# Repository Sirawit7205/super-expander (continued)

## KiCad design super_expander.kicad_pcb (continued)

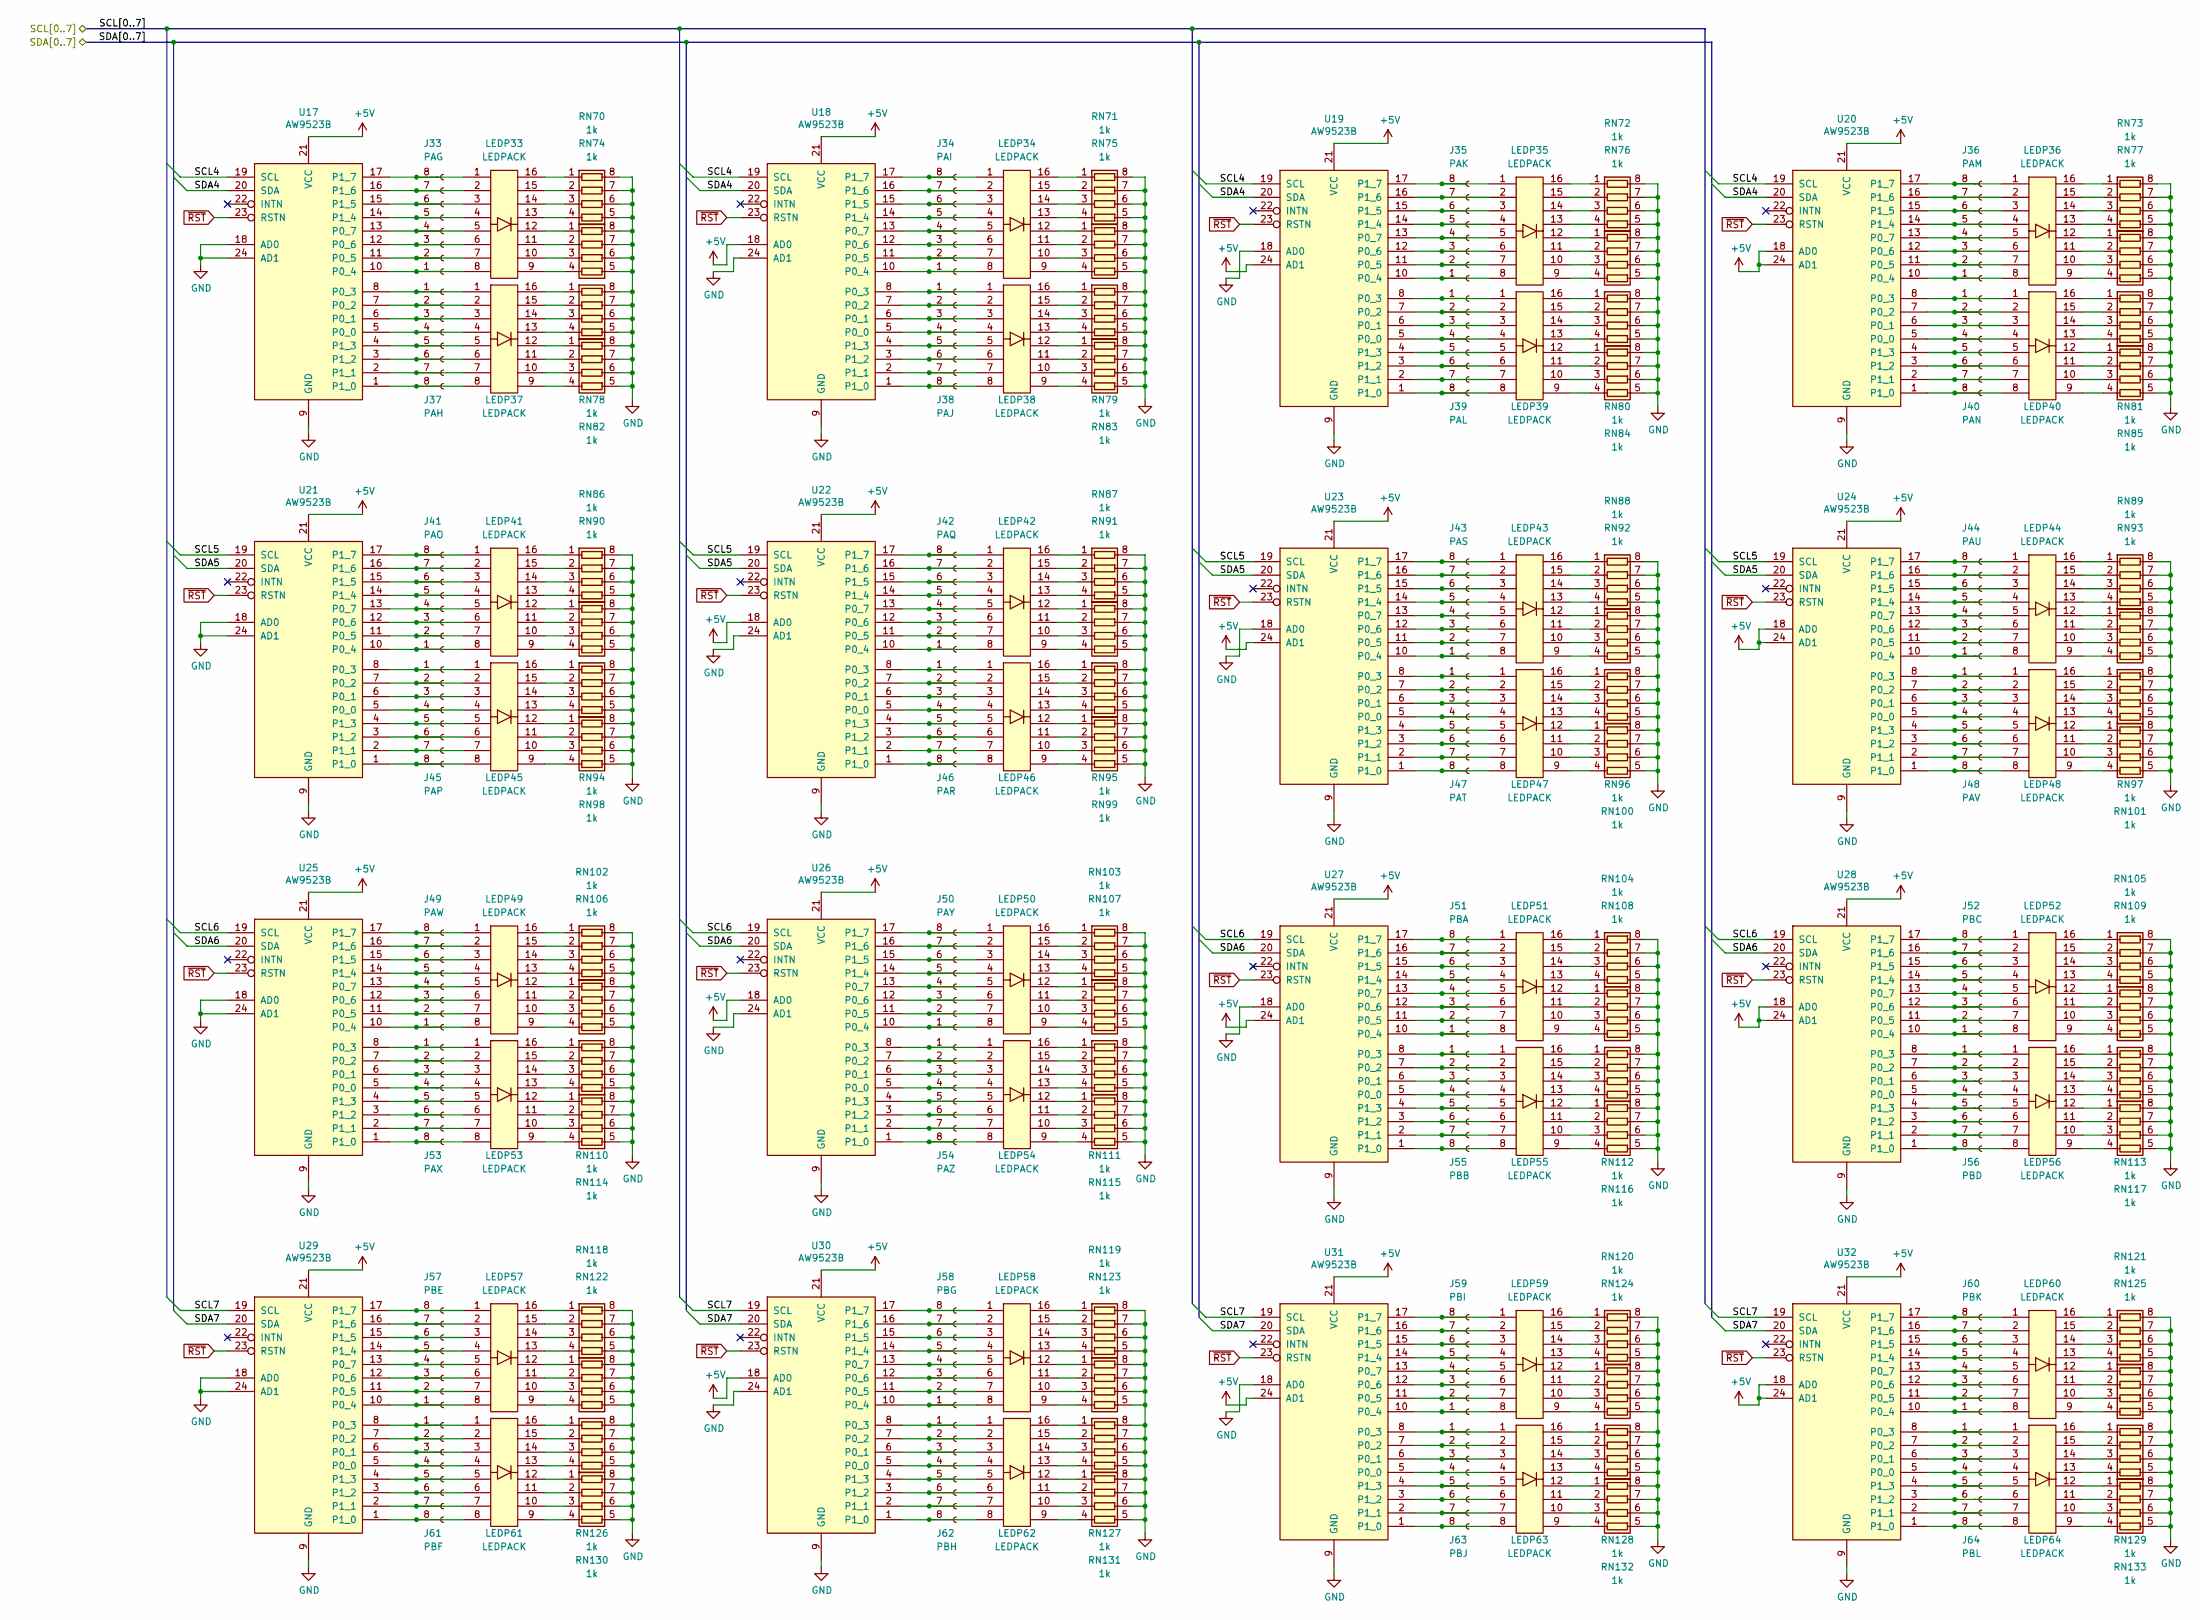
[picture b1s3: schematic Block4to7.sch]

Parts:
J33: PAG; PinHeader_1x08_P1.27mm_Vertical
J34: PAI; PinHeader_1x08_P1.27mm_Vertical
J35: PAK; PinHeader_1x08_P1.27mm_Vertical
J36: PAM; PinHeader_1x08_P1.27mm_Vertical
J37: PAH; PinHeader_1x08_P1.27mm_Vertical
J38: PAJ; PinHeader_1x08_P1.27mm_Vertical
J39: PAL; PinHeader_1x08_P1.27mm_Vertical
J40: PAN; PinHeader_1x08_P1.27mm_Vertical
J41: PAO; PinHeader_1x08_P1.27mm_Vertical
J42: PAQ; PinHeader_1x08_P1.27mm_Vertical
J43: PAS; PinHeader_1x08_P1.27mm_Vertical
J44: PAU; PinHeader_1x08_P1.27mm_Vertical
J45: PAP; PinHeader_1x08_P1.27mm_Vertical
J46: PAR; PinHeader_1x08_P1.27mm_Vertical
J47: PAT; PinHeader_1x08_P1.27mm_Vertical
J48: PAV; PinHeader_1x08_P1.27mm_Vertical
J49: PAW; PinHeader_1x08_P1.27mm_Vertical
J50: PAY; PinHeader_1x08_P1.27mm_Vertical
J51: PBA; PinHeader_1x08_P1.27mm_Vertical
J52: PBC; PinHeader_1x08_P1.27mm_Vertical
J53: PAX; PinHeader_1x08_P1.27mm_Vertical
J54: PAZ; PinHeader_1x08_P1.27mm_Vertical
J55: PBB; PinHeader_1x08_P1.27mm_Vertical
J56: PBD; PinHeader_1x08_P1.27mm_Vertical
J57: PBE; PinHeader_1x08_P1.27mm_Vertical
J58: PBG; PinHeader_1x08_P1.27mm_Vertical
J59: PBI; PinHeader_1x08_P1.27mm_Vertical
J60: PBK; PinHeader_1x08_P1.27mm_Vertical
J61: PBF; PinHeader_1x08_P1.27mm_Vertical
J62: PBH; PinHeader_1x08_P1.27mm_Vertical
J63: PBJ; PinHeader_1x08_P1.27mm_Vertical
J64: PBL; PinHeader_1x08_P1.27mm_Vertical
LEDP33, LEDP34, LEDP35, LEDP36, LEDP37, LEDP38, LEDP39, LEDP40, LEDP41, LEDP42, LEDP43, LEDP44, LEDP45, LEDP46, LEDP47, LEDP48, LEDP49, LEDP50, LEDP51, LEDP52, LEDP53, LEDP54, LEDP55, LEDP56, LEDP57, LEDP58, LEDP59, LEDP60, LEDP61, LEDP62, LEDP63, LEDP64: LEDPACK; LED_PACK_8
RN70, RN71, RN72, RN73, RN74, RN75, RN76, RN77, RN78, RN79, RN80, RN81, RN82, RN83, RN84, RN85, RN86, RN87, RN88, RN89, RN90, RN91, RN92, RN93, RN94, RN95, RN96, RN97, RN98, RN99, RN100, RN101, RN102, RN103, RN104, RN105, RN106, RN107, RN108, RN109, RN110, RN111, RN112, RN113, RN114, RN115, RN116, RN117, RN118, RN119, RN120, RN121, RN122, RN123, RN124, RN125, RN126, RN127, RN128, RN129, RN130, RN131, RN132, RN133: 1k; R_Array_Convex_4x0402
U17, U18, U19, U20, U21, U22, U23, U24, U25, U26, U27, U28, U29, U30, U31, U32: AW9523B; QFN-24-1EP_4x4mm_P0.5mm_EP2.7x2.7mm_ThermalVias

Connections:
+5V: U17.21 (VCC), U18.18 (AD0), U18.21 (VCC), U19.21 (VCC), U19.24 (AD1), U20.18 (AD0), U20.21 (VCC), U20.24 (AD1), U21.21 (VCC), U22.18 (AD0), U22.21 (VCC), U23.21 (VCC), U23.24 (AD1), U24.18 (AD0), U24.21 (VCC), U24.24 (AD1), U25.21 (VCC), U26.18 (AD0), U26.21 (VCC), U27.21 (VCC), U27.24 (AD1), U28.18 (AD0), U28.21 (VCC), U28.24 (AD1), U29.21 (VCC), U30.18 (AD0), U30.21 (VCC), U31.21 (VCC), U31.24 (AD1), U32.18 (AD0), U32.21 (VCC), U32.24 (AD1); also elsewhere on the board
/SCL4: U17.19 (SCL), U18.19 (SCL), U19.19 (SCL), U20.19 (SCL); also elsewhere on the board
/SCL5: U21.19 (SCL), U22.19 (SCL), U23.19 (SCL), U24.19 (SCL); also elsewhere on the board
/SCL6: U25.19 (SCL), U26.19 (SCL), U27.19 (SCL), U28.19 (SCL); also elsewhere on the board
/SCL7: U29.19 (SCL), U30.19 (SCL), U31.19 (SCL), U32.19 (SCL); also elsewhere on the board
/SDA4: U17.20 (SDA), U18.20 (SDA), U19.20 (SDA), U20.20 (SDA); also elsewhere on the board
/SDA5: U21.20 (SDA), U22.20 (SDA), U23.20 (SDA), U24.20 (SDA); also elsewhere on the board
/SDA6: U25.20 (SDA), U26.20 (SDA), U27.20 (SDA), U28.20 (SDA); also elsewhere on the board
/SDA7: U29.20 (SDA), U30.20 (SDA), U31.20 (SDA), U32.20 (SDA); also elsewhere on the board
GND: RN70.5 (R4.2), RN70.6 (R3.2), RN70.7 (R2.2), RN70.8 (R1.2), RN71.5 (R4.2), RN71.6 (R3.2), RN71.7 (R2.2), RN71.8 (R1.2), RN72.5 (R4.2), RN72.6 (R3.2), RN72.7 (R2.2), RN72.8 (R1.2), RN73.5 (R4.2), RN73.6 (R3.2), RN73.7 (R2.2), RN73.8 (R1.2), RN74.5 (R4.2), RN74.6 (R3.2), RN74.7 (R2.2), RN74.8 (R1.2), RN75.5 (R4.2), RN75.6 (R3.2), RN75.7 (R2.2), RN75.8 (R1.2), RN76.5 (R4.2), RN76.6 (R3.2), RN76.7 (R2.2), RN76.8 (R1.2), RN77.5 (R4.2), RN77.6 (R3.2), RN77.7 (R2.2), RN77.8 (R1.2), RN78.5 (R4.2), RN78.6 (R3.2), RN78.7 (R2.2), RN78.8 (R1.2), RN79.5 (R4.2), RN79.6 (R3.2), RN79.7 (R2.2), RN79.8 (R1.2), RN80.5 (R4.2), RN80.6 (R3.2), RN80.7 (R2.2), RN80.8 (R1.2), RN81.5 (R4.2), RN81.6 (R3.2), RN81.7 (R2.2), RN81.8 (R1.2), RN82.5 (R4.2), RN82.6 (R3.2), RN82.7 (R2.2), RN82.8 (R1.2), RN83.5 (R4.2), RN83.6 (R3.2), RN83.7 (R2.2), RN83.8 (R1.2), RN84.5 (R4.2), RN84.6 (R3.2), RN84.7 (R2.2), RN84.8 (R1.2), RN85.5 (R4.2), RN85.6 (R3.2), RN85.7 (R2.2), RN85.8 (R1.2), RN86.5 (R4.2), RN86.6 (R3.2), RN86.7 (R2.2), RN86.8 (R1.2), RN87.5 (R4.2), RN87.6 (R3.2), RN87.7 (R2.2), RN87.8 (R1.2), RN88.5 (R4.2), RN88.6 (R3.2), RN88.7 (R2.2), RN88.8 (R1.2), RN89.5 (R4.2), RN89.6 (R3.2), RN89.7 (R2.2), RN89.8 (R1.2), RN90.5 (R4.2), RN90.6 (R3.2), RN90.7 (R2.2), RN90.8 (R1.2), RN91.5 (R4.2), RN91.6 (R3.2), RN91.7 (R2.2), RN91.8 (R1.2), RN92.5 (R4.2), RN92.6 (R3.2), RN92.7 (R2.2), RN92.8 (R1.2), RN93.5 (R4.2), RN93.6 (R3.2), RN93.7 (R2.2), RN93.8 (R1.2), RN94.5 (R4.2), RN94.6 (R3.2), RN94.7 (R2.2), RN94.8 (R1.2), RN95.5 (R4.2), RN95.6 (R3.2), RN95.7 (R2.2), RN95.8 (R1.2), RN96.5 (R4.2), RN96.6 (R3.2), RN96.7 (R2.2), RN96.8 (R1.2), RN97.5 (R4.2), RN97.6 (R3.2), RN97.7 (R2.2), RN97.8 (R1.2), RN98.5 (R4.2), RN98.6 (R3.2), RN98.7 (R2.2), RN98.8 (R1.2), RN99.5 (R4.2), RN99.6 (R3.2), RN99.7 (R2.2), RN99.8 (R1.2), RN100.5 (R4.2), RN100.6 (R3.2), RN100.7 (R2.2), RN100.8 (R1.2), RN101.5 (R4.2), RN101.6 (R3.2), RN101.7 (R2.2), RN101.8 (R1.2), RN102.5 (R4.2), RN102.6 (R3.2), RN102.7 (R2.2), RN102.8 (R1.2), RN103.5 (R4.2), RN103.6 (R3.2), RN103.7 (R2.2), RN103.8 (R1.2), RN104.5 (R4.2), RN104.6 (R3.2), RN104.7 (R2.2), RN104.8 (R1.2), RN105.5 (R4.2), RN105.6 (R3.2), RN105.7 (R2.2), RN105.8 (R1.2), RN106.5 (R4.2), RN106.6 (R3.2), RN106.7 (R2.2), RN106.8 (R1.2), RN107.5 (R4.2), RN107.6 (R3.2), RN107.7 (R2.2), RN107.8 (R1.2), RN108.5 (R4.2), RN108.6 (R3.2), RN108.7 (R2.2), RN108.8 (R1.2), RN109.5 (R4.2), RN109.6 (R3.2), RN109.7 (R2.2), RN109.8 (R1.2), RN110.5 (R4.2), RN110.6 (R3.2), RN110.7 (R2.2), RN110.8 (R1.2), RN111.5 (R4.2), RN111.6 (R3.2), RN111.7 (R2.2), RN111.8 (R1.2), RN112.5 (R4.2), RN112.6 (R3.2), RN112.7 (R2.2), RN112.8 (R1.2), RN113.5 (R4.2), RN113.6 (R3.2), RN113.7 (R2.2), RN113.8 (R1.2), RN114.5 (R4.2), RN114.6 (R3.2), RN114.7 (R2.2), RN114.8 (R1.2), RN115.5 (R4.2), RN115.6 (R3.2), RN115.7 (R2.2), RN115.8 (R1.2), RN116.5 (R4.2), RN116.6 (R3.2), RN116.7 (R2.2), RN116.8 (R1.2), RN117.5 (R4.2), RN117.6 (R3.2), RN117.7 (R2.2), RN117.8 (R1.2), RN118.5 (R4.2), RN118.6 (R3.2), RN118.7 (R2.2), RN118.8 (R1.2), RN119.5 (R4.2), RN119.6 (R3.2), RN119.7 (R2.2), RN119.8 (R1.2), RN120.5 (R4.2), RN120.6 (R3.2), RN120.7 (R2.2), RN120.8 (R1.2), RN121.5 (R4.2), RN121.6 (R3.2), RN121.7 (R2.2), RN121.8 (R1.2), RN122.5 (R4.2), RN122.6 (R3.2), RN122.7 (R2.2), RN122.8 (R1.2), RN123.5 (R4.2), RN123.6 (R3.2), RN123.7 (R2.2), RN123.8 (R1.2), RN124.5 (R4.2), RN124.6 (R3.2), RN124.7 (R2.2), RN124.8 (R1.2), RN125.5 (R4.2), RN125.6 (R3.2), RN125.7 (R2.2), RN125.8 (R1.2), RN126.5 (R4.2), RN126.6 (R3.2), RN126.7 (R2.2), RN126.8 (R1.2), RN127.5 (R4.2), RN127.6 (R3.2), RN127.7 (R2.2), RN127.8 (R1.2), RN128.5 (R4.2), RN128.6 (R3.2), RN128.7 (R2.2), RN128.8 (R1.2), RN129.5 (R4.2), RN129.6 (R3.2), RN129.7 (R2.2), RN129.8 (R1.2), RN130.5 (R4.2), RN130.6 (R3.2), RN130.7 (R2.2), RN130.8 (R1.2), RN131.5 (R4.2), RN131.6 (R3.2), RN131.7 (R2.2), RN131.8 (R1.2), RN132.5 (R4.2), RN132.6 (R3.2), RN132.7 (R2.2), RN132.8 (R1.2), RN133.5 (R4.2), RN133.6 (R3.2), RN133.7 (R2.2), RN133.8 (R1.2), U17.9 (GND), U17.18 (AD0), U17.24 (AD1), U17.25 (GND), U18.9 (GND), U18.24 (AD1), U18.25 (GND), U19.9 (GND), U19.18 (AD0), U19.25 (GND), U20.9 (GND), U20.25 (GND), U21.9 (GND), U21.18 (AD0), U21.24 (AD1), U21.25 (GND), U22.9 (GND), U22.24 (AD1), U22.25 (GND), U23.9 (GND), U23.18 (AD0), U23.25 (GND), U24.9 (GND), U24.25 (GND), U25.9 (GND), U25.18 (AD0), U25.24 (AD1), U25.25 (GND), U26.9 (GND), U26.24 (AD1), U26.25 (GND), U27.9 (GND), U27.18 (AD0), U27.25 (GND), U28.9 (GND), U28.25 (GND), U29.9 (GND), U29.18 (AD0), U29.24 (AD1), U29.25 (GND), U30.9 (GND), U30.24 (AD1), U30.25 (GND), U31.9 (GND), U31.18 (AD0), U31.25 (GND), U32.9 (GND), U32.25 (GND); also elsewhere on the board
unnamed: J33.1, LEDP33.8, U17.10 (P0_4)
unnamed: J33.2, LEDP33.7, U17.11 (P0_5)
unnamed: J33.3, LEDP33.6, U17.12 (P0_6)
unnamed: J33.4, LEDP33.5, U17.13 (P0_7)
unnamed: J33.5, LEDP33.4, U17.14 (P1_4)
unnamed: J33.6, LEDP33.3, U17.15 (P1_5)
unnamed: J33.7, LEDP33.2, U17.16 (P1_6)
unnamed: J33.8, LEDP33.1, U17.17 (P1_7)
unnamed: J34.1, LEDP34.8, U18.10 (P0_4)
unnamed: J34.2, LEDP34.7, U18.11 (P0_5)
unnamed: J34.3, LEDP34.6, U18.12 (P0_6)
unnamed: J34.4, LEDP34.5, U18.13 (P0_7)
unnamed: J34.5, LEDP34.4, U18.14 (P1_4)
unnamed: J34.6, LEDP34.3, U18.15 (P1_5)
unnamed: J34.7, LEDP34.2, U18.16 (P1_6)
unnamed: J34.8, LEDP34.1, U18.17 (P1_7)
unnamed: J35.1, LEDP35.8, U19.10 (P0_4)
unnamed: J35.2, LEDP35.7, U19.11 (P0_5)
unnamed: J35.3, LEDP35.6, U19.12 (P0_6)
unnamed: J35.4, LEDP35.5, U19.13 (P0_7)
unnamed: J35.5, LEDP35.4, U19.14 (P1_4)
unnamed: J35.6, LEDP35.3, U19.15 (P1_5)
unnamed: J35.7, LEDP35.2, U19.16 (P1_6)
unnamed: J35.8, LEDP35.1, U19.17 (P1_7)
unnamed: J36.1, LEDP36.8, U20.10 (P0_4)
unnamed: J36.2, LEDP36.7, U20.11 (P0_5)
unnamed: J36.3, LEDP36.6, U20.12 (P0_6)
unnamed: J36.4, LEDP36.5, U20.13 (P0_7)
unnamed: J36.5, LEDP36.4, U20.14 (P1_4)
unnamed: J36.6, LEDP36.3, U20.15 (P1_5)
unnamed: J36.7, LEDP36.2, U20.16 (P1_6)
unnamed: J36.8, LEDP36.1, U20.17 (P1_7)
unnamed: J37.1, LEDP37.1, U17.8 (P0_3)
unnamed: J37.2, LEDP37.2, U17.7 (P0_2)
unnamed: J37.3, LEDP37.3, U17.6 (P0_1)
unnamed: J37.4, LEDP37.4, U17.5 (P0_0)
unnamed: J37.5, LEDP37.5, U17.4 (P1_3)
unnamed: J37.6, LEDP37.6, U17.3 (P1_2)
unnamed: J37.7, LEDP37.7, U17.2 (P1_1)
unnamed: J37.8, LEDP37.8, U17.1 (P1_0)
unnamed: J38.1, LEDP38.1, U18.8 (P0_3)
unnamed: J38.2, LEDP38.2, U18.7 (P0_2)
unnamed: J38.3, LEDP38.3, U18.6 (P0_1)
unnamed: J38.4, LEDP38.4, U18.5 (P0_0)
unnamed: J38.5, LEDP38.5, U18.4 (P1_3)
unnamed: J38.6, LEDP38.6, U18.3 (P1_2)
unnamed: J38.7, LEDP38.7, U18.2 (P1_1)
unnamed: J38.8, LEDP38.8, U18.1 (P1_0)
unnamed: J39.1, LEDP39.1, U19.8 (P0_3)
unnamed: J39.2, LEDP39.2, U19.7 (P0_2)
unnamed: J39.3, LEDP39.3, U19.6 (P0_1)
unnamed: J39.4, LEDP39.4, U19.5 (P0_0)
unnamed: J39.5, LEDP39.5, U19.4 (P1_3)
unnamed: J39.6, LEDP39.6, U19.3 (P1_2)
unnamed: J39.7, LEDP39.7, U19.2 (P1_1)
unnamed: J39.8, LEDP39.8, U19.1 (P1_0)
unnamed: J40.1, LEDP40.1, U20.8 (P0_3)
unnamed: J40.2, LEDP40.2, U20.7 (P0_2)
unnamed: J40.3, LEDP40.3, U20.6 (P0_1)
unnamed: J40.4, LEDP40.4, U20.5 (P0_0)
unnamed: J40.5, LEDP40.5, U20.4 (P1_3)
unnamed: J40.6, LEDP40.6, U20.3 (P1_2)
unnamed: J40.7, LEDP40.7, U20.2 (P1_1)
unnamed: J40.8, LEDP40.8, U20.1 (P1_0)
unnamed: J41.1, LEDP41.8, U21.10 (P0_4)
unnamed: J41.2, LEDP41.7, U21.11 (P0_5)
unnamed: J41.3, LEDP41.6, U21.12 (P0_6)
unnamed: J41.4, LEDP41.5, U21.13 (P0_7)
unnamed: J41.5, LEDP41.4, U21.14 (P1_4)
unnamed: J41.6, LEDP41.3, U21.15 (P1_5)
unnamed: J41.7, LEDP41.2, U21.16 (P1_6)
unnamed: J41.8, LEDP41.1, U21.17 (P1_7)
unnamed: J42.1, LEDP42.8, U22.10 (P0_4)
unnamed: J42.2, LEDP42.7, U22.11 (P0_5)
unnamed: J42.3, LEDP42.6, U22.12 (P0_6)
unnamed: J42.4, LEDP42.5, U22.13 (P0_7)
unnamed: J42.5, LEDP42.4, U22.14 (P1_4)
unnamed: J42.6, LEDP42.3, U22.15 (P1_5)
unnamed: J42.7, LEDP42.2, U22.16 (P1_6)
unnamed: J42.8, LEDP42.1, U22.17 (P1_7)
unnamed: J43.1, LEDP43.8, U23.10 (P0_4)
unnamed: J43.2, LEDP43.7, U23.11 (P0_5)
unnamed: J43.3, LEDP43.6, U23.12 (P0_6)
unnamed: J43.4, LEDP43.5, U23.13 (P0_7)
unnamed: J43.5, LEDP43.4, U23.14 (P1_4)
unnamed: J43.6, LEDP43.3, U23.15 (P1_5)
unnamed: J43.7, LEDP43.2, U23.16 (P1_6)
unnamed: J43.8, LEDP43.1, U23.17 (P1_7)
unnamed: J44.1, LEDP44.8, U24.10 (P0_4)
unnamed: J44.2, LEDP44.7, U24.11 (P0_5)
unnamed: J44.3, LEDP44.6, U24.12 (P0_6)
unnamed: J44.4, LEDP44.5, U24.13 (P0_7)
unnamed: J44.5, LEDP44.4, U24.14 (P1_4)
unnamed: J44.6, LEDP44.3, U24.15 (P1_5)
unnamed: J44.7, LEDP44.2, U24.16 (P1_6)
unnamed: J44.8, LEDP44.1, U24.17 (P1_7)
unnamed: J45.1, LEDP45.1, U21.8 (P0_3)
unnamed: J45.2, LEDP45.2, U21.7 (P0_2)
unnamed: J45.3, LEDP45.3, U21.6 (P0_1)
unnamed: J45.4, LEDP45.4, U21.5 (P0_0)
unnamed: J45.5, LEDP45.5, U21.4 (P1_3)
unnamed: J45.6, LEDP45.6, U21.3 (P1_2)
unnamed: J45.7, LEDP45.7, U21.2 (P1_1)
unnamed: J45.8, LEDP45.8, U21.1 (P1_0)
unnamed: J46.1, LEDP46.1, U22.8 (P0_3)
unnamed: J46.2, LEDP46.2, U22.7 (P0_2)
unnamed: J46.3, LEDP46.3, U22.6 (P0_1)
unnamed: J46.4, LEDP46.4, U22.5 (P0_0)
unnamed: J46.5, LEDP46.5, U22.4 (P1_3)
unnamed: J46.6, LEDP46.6, U22.3 (P1_2)
unnamed: J46.7, LEDP46.7, U22.2 (P1_1)
unnamed: J46.8, LEDP46.8, U22.1 (P1_0)
unnamed: J47.1, LEDP47.1, U23.8 (P0_3)
unnamed: J47.2, LEDP47.2, U23.7 (P0_2)
unnamed: J47.3, LEDP47.3, U23.6 (P0_1)
unnamed: J47.4, LEDP47.4, U23.5 (P0_0)
unnamed: J47.5, LEDP47.5, U23.4 (P1_3)
unnamed: J47.6, LEDP47.6, U23.3 (P1_2)
unnamed: J47.7, LEDP47.7, U23.2 (P1_1)
unnamed: J47.8, LEDP47.8, U23.1 (P1_0)
unnamed: J48.1, LEDP48.1, U24.8 (P0_3)
unnamed: J48.2, LEDP48.2, U24.7 (P0_2)
unnamed: J48.3, LEDP48.3, U24.6 (P0_1)
unnamed: J48.4, LEDP48.4, U24.5 (P0_0)
unnamed: J48.5, LEDP48.5, U24.4 (P1_3)
unnamed: J48.6, LEDP48.6, U24.3 (P1_2)
unnamed: J48.7, LEDP48.7, U24.2 (P1_1)
unnamed: J48.8, LEDP48.8, U24.1 (P1_0)
unnamed: J49.1, LEDP49.8, U25.10 (P0_4)
unnamed: J49.2, LEDP49.7, U25.11 (P0_5)
unnamed: J49.3, LEDP49.6, U25.12 (P0_6)
unnamed: J49.4, LEDP49.5, U25.13 (P0_7)
unnamed: J49.5, LEDP49.4, U25.14 (P1_4)
unnamed: J49.6, LEDP49.3, U25.15 (P1_5)
unnamed: J49.7, LEDP49.2, U25.16 (P1_6)
unnamed: J49.8, LEDP49.1, U25.17 (P1_7)
unnamed: J50.1, LEDP50.8, U26.10 (P0_4)
unnamed: J50.2, LEDP50.7, U26.11 (P0_5)
unnamed: J50.3, LEDP50.6, U26.12 (P0_6)
unnamed: J50.4, LEDP50.5, U26.13 (P0_7)
unnamed: J50.5, LEDP50.4, U26.14 (P1_4)
unnamed: J50.6, LEDP50.3, U26.15 (P1_5)
unnamed: J50.7, LEDP50.2, U26.16 (P1_6)
unnamed: J50.8, LEDP50.1, U26.17 (P1_7)
unnamed: J51.1, LEDP51.8, U27.10 (P0_4)
unnamed: J51.2, LEDP51.7, U27.11 (P0_5)
unnamed: J51.3, LEDP51.6, U27.12 (P0_6)
unnamed: J51.4, LEDP51.5, U27.13 (P0_7)
unnamed: J51.5, LEDP51.4, U27.14 (P1_4)
unnamed: J51.6, LEDP51.3, U27.15 (P1_5)
unnamed: J51.7, LEDP51.2, U27.16 (P1_6)
unnamed: J51.8, LEDP51.1, U27.17 (P1_7)
unnamed: J52.1, LEDP52.8, U28.10 (P0_4)
unnamed: J52.2, LEDP52.7, U28.11 (P0_5)
unnamed: J52.3, LEDP52.6, U28.12 (P0_6)
unnamed: J52.4, LEDP52.5, U28.13 (P0_7)
unnamed: J52.5, LEDP52.4, U28.14 (P1_4)
unnamed: J52.6, LEDP52.3, U28.15 (P1_5)
unnamed: J52.7, LEDP52.2, U28.16 (P1_6)
unnamed: J52.8, LEDP52.1, U28.17 (P1_7)
unnamed: J53.1, LEDP53.1, U25.8 (P0_3)
unnamed: J53.2, LEDP53.2, U25.7 (P0_2)
unnamed: J53.3, LEDP53.3, U25.6 (P0_1)
unnamed: J53.4, LEDP53.4, U25.5 (P0_0)
unnamed: J53.5, LEDP53.5, U25.4 (P1_3)
unnamed: J53.6, LEDP53.6, U25.3 (P1_2)
unnamed: J53.7, LEDP53.7, U25.2 (P1_1)
unnamed: J53.8, LEDP53.8, U25.1 (P1_0)
unnamed: J54.1, LEDP54.1, U26.8 (P0_3)
unnamed: J54.2, LEDP54.2, U26.7 (P0_2)
unnamed: J54.3, LEDP54.3, U26.6 (P0_1)
unnamed: J54.4, LEDP54.4, U26.5 (P0_0)
unnamed: J54.5, LEDP54.5, U26.4 (P1_3)
unnamed: J54.6, LEDP54.6, U26.3 (P1_2)
unnamed: J54.7, LEDP54.7, U26.2 (P1_1)
unnamed: J54.8, LEDP54.8, U26.1 (P1_0)
unnamed: J55.1, LEDP55.1, U27.8 (P0_3)
unnamed: J55.2, LEDP55.2, U27.7 (P0_2)
unnamed: J55.3, LEDP55.3, U27.6 (P0_1)
unnamed: J55.4, LEDP55.4, U27.5 (P0_0)
unnamed: J55.5, LEDP55.5, U27.4 (P1_3)
unnamed: J55.6, LEDP55.6, U27.3 (P1_2)
unnamed: J55.7, LEDP55.7, U27.2 (P1_1)
unnamed: J55.8, LEDP55.8, U27.1 (P1_0)
unnamed: J56.1, LEDP56.1, U28.8 (P0_3)
unnamed: J56.2, LEDP56.2, U28.7 (P0_2)
unnamed: J56.3, LEDP56.3, U28.6 (P0_1)
unnamed: J56.4, LEDP56.4, U28.5 (P0_0)
unnamed: J56.5, LEDP56.5, U28.4 (P1_3)
unnamed: J56.6, LEDP56.6, U28.3 (P1_2)
unnamed: J56.7, LEDP56.7, U28.2 (P1_1)
unnamed: J56.8, LEDP56.8, U28.1 (P1_0)
unnamed: J57.1, LEDP57.8, U29.10 (P0_4)
unnamed: J57.2, LEDP57.7, U29.11 (P0_5)
unnamed: J57.3, LEDP57.6, U29.12 (P0_6)
unnamed: J57.4, LEDP57.5, U29.13 (P0_7)
unnamed: J57.5, LEDP57.4, U29.14 (P1_4)
unnamed: J57.6, LEDP57.3, U29.15 (P1_5)
unnamed: J57.7, LEDP57.2, U29.16 (P1_6)
unnamed: J57.8, LEDP57.1, U29.17 (P1_7)
unnamed: J58.1, LEDP58.8, U30.10 (P0_4)
unnamed: J58.2, LEDP58.7, U30.11 (P0_5)
unnamed: J58.3, LEDP58.6, U30.12 (P0_6)
unnamed: J58.4, LEDP58.5, U30.13 (P0_7)
unnamed: J58.5, LEDP58.4, U30.14 (P1_4)
unnamed: J58.6, LEDP58.3, U30.15 (P1_5)
unnamed: J58.7, LEDP58.2, U30.16 (P1_6)
unnamed: J58.8, LEDP58.1, U30.17 (P1_7)
unnamed: J59.1, LEDP59.8, U31.10 (P0_4)
unnamed: J59.2, LEDP59.7, U31.11 (P0_5)
unnamed: J59.3, LEDP59.6, U31.12 (P0_6)
unnamed: J59.4, LEDP59.5, U31.13 (P0_7)
unnamed: J59.5, LEDP59.4, U31.14 (P1_4)
unnamed: J59.6, LEDP59.3, U31.15 (P1_5)
unnamed: J59.7, LEDP59.2, U31.16 (P1_6)
unnamed: J59.8, LEDP59.1, U31.17 (P1_7)
unnamed: J60.1, LEDP60.8, U32.10 (P0_4)
unnamed: J60.2, LEDP60.7, U32.11 (P0_5)
unnamed: J60.3, LEDP60.6, U32.12 (P0_6)
unnamed: J60.4, LEDP60.5, U32.13 (P0_7)
unnamed: J60.5, LEDP60.4, U32.14 (P1_4)
unnamed: J60.6, LEDP60.3, U32.15 (P1_5)
unnamed: J60.7, LEDP60.2, U32.16 (P1_6)
unnamed: J60.8, LEDP60.1, U32.17 (P1_7)
unnamed: J61.1, LEDP61.1, U29.8 (P0_3)
unnamed: J61.2, LEDP61.2, U29.7 (P0_2)
unnamed: J61.3, LEDP61.3, U29.6 (P0_1)
unnamed: J61.4, LEDP61.4, U29.5 (P0_0)
unnamed: J61.5, LEDP61.5, U29.4 (P1_3)
unnamed: J61.6, LEDP61.6, U29.3 (P1_2)
unnamed: J61.7, LEDP61.7, U29.2 (P1_1)
unnamed: J61.8, LEDP61.8, U29.1 (P1_0)
unnamed: J62.1, LEDP62.1, U30.8 (P0_3)
unnamed: J62.2, LEDP62.2, U30.7 (P0_2)
unnamed: J62.3, LEDP62.3, U30.6 (P0_1)
unnamed: J62.4, LEDP62.4, U30.5 (P0_0)
unnamed: J62.5, LEDP62.5, U30.4 (P1_3)
unnamed: J62.6, LEDP62.6, U30.3 (P1_2)
unnamed: J62.7, LEDP62.7, U30.2 (P1_1)
unnamed: J62.8, LEDP62.8, U30.1 (P1_0)
unnamed: J63.1, LEDP63.1, U31.8 (P0_3)
unnamed: J63.2, LEDP63.2, U31.7 (P0_2)
unnamed: J63.3, LEDP63.3, U31.6 (P0_1)
unnamed: J63.4, LEDP63.4, U31.5 (P0_0)
unnamed: J63.5, LEDP63.5, U31.4 (P1_3)
unnamed: J63.6, LEDP63.6, U31.3 (P1_2)
unnamed: J63.7, LEDP63.7, U31.2 (P1_1)
unnamed: J63.8, LEDP63.8, U31.1 (P1_0)
unnamed: J64.1, LEDP64.1, U32.8 (P0_3)
unnamed: J64.2, LEDP64.2, U32.7 (P0_2)
unnamed: J64.3, LEDP64.3, U32.6 (P0_1)
unnamed: J64.4, LEDP64.4, U32.5 (P0_0)
unnamed: J64.5, LEDP64.5, U32.4 (P1_3)
unnamed: J64.6, LEDP64.6, U32.3 (P1_2)
unnamed: J64.7, LEDP64.7, U32.2 (P1_1)
unnamed: J64.8, LEDP64.8, U32.1 (P1_0)
unnamed: LEDP33.9, RN74.4 (R4.1)
unnamed: LEDP33.10, RN74.3 (R3.1)
unnamed: LEDP33.11, RN74.2 (R2.1)
unnamed: LEDP33.12, RN74.1 (R1.1)
unnamed: LEDP33.13, RN70.4 (R4.1)
unnamed: LEDP33.14, RN70.3 (R3.1)
unnamed: LEDP33.15, RN70.2 (R2.1)
unnamed: LEDP33.16, RN70.1 (R1.1)
unnamed: LEDP34.9, RN75.4 (R4.1)
unnamed: LEDP34.10, RN75.3 (R3.1)
unnamed: LEDP34.11, RN75.2 (R2.1)
unnamed: LEDP34.12, RN75.1 (R1.1)
unnamed: LEDP34.13, RN71.4 (R4.1)
unnamed: LEDP34.14, RN71.3 (R3.1)
unnamed: LEDP34.15, RN71.2 (R2.1)
unnamed: LEDP34.16, RN71.1 (R1.1)
unnamed: LEDP35.9, RN76.4 (R4.1)
unnamed: LEDP35.10, RN76.3 (R3.1)
unnamed: LEDP35.11, RN76.2 (R2.1)
unnamed: LEDP35.12, RN76.1 (R1.1)
unnamed: LEDP35.13, RN72.4 (R4.1)
unnamed: LEDP35.14, RN72.3 (R3.1)
unnamed: LEDP35.15, RN72.2 (R2.1)
unnamed: LEDP35.16, RN72.1 (R1.1)
unnamed: LEDP36.9, RN77.4 (R4.1)
unnamed: LEDP36.10, RN77.3 (R3.1)
unnamed: LEDP36.11, RN77.2 (R2.1)
unnamed: LEDP36.12, RN77.1 (R1.1)
unnamed: LEDP36.13, RN73.4 (R4.1)
unnamed: LEDP36.14, RN73.3 (R3.1)
unnamed: LEDP36.15, RN73.2 (R2.1)
unnamed: LEDP36.16, RN73.1 (R1.1)
unnamed: LEDP37.9, RN82.4 (R4.1)
unnamed: LEDP37.10, RN82.3 (R3.1)
unnamed: LEDP37.11, RN82.2 (R2.1)
unnamed: LEDP37.12, RN82.1 (R1.1)
unnamed: LEDP37.13, RN78.4 (R4.1)
unnamed: LEDP37.14, RN78.3 (R3.1)
unnamed: LEDP37.15, RN78.2 (R2.1)
unnamed: LEDP37.16, RN78.1 (R1.1)
unnamed: LEDP38.9, RN83.4 (R4.1)
unnamed: LEDP38.10, RN83.3 (R3.1)
unnamed: LEDP38.11, RN83.2 (R2.1)
unnamed: LEDP38.12, RN83.1 (R1.1)
unnamed: LEDP38.13, RN79.4 (R4.1)
unnamed: LEDP38.14, RN79.3 (R3.1)
unnamed: LEDP38.15, RN79.2 (R2.1)
unnamed: LEDP38.16, RN79.1 (R1.1)
unnamed: LEDP39.9, RN84.4 (R4.1)
unnamed: LEDP39.10, RN84.3 (R3.1)
unnamed: LEDP39.11, RN84.2 (R2.1)
unnamed: LEDP39.12, RN84.1 (R1.1)
unnamed: LEDP39.13, RN80.4 (R4.1)
unnamed: LEDP39.14, RN80.3 (R3.1)
unnamed: LEDP39.15, RN80.2 (R2.1)
unnamed: LEDP39.16, RN80.1 (R1.1)
unnamed: LEDP40.9, RN85.4 (R4.1)
unnamed: LEDP40.10, RN85.3 (R3.1)
unnamed: LEDP40.11, RN85.2 (R2.1)
unnamed: LEDP40.12, RN85.1 (R1.1)
unnamed: LEDP40.13, RN81.4 (R4.1)
unnamed: LEDP40.14, RN81.3 (R3.1)
unnamed: LEDP40.15, RN81.2 (R2.1)
unnamed: LEDP40.16, RN81.1 (R1.1)
unnamed: LEDP41.9, RN90.4 (R4.1)
unnamed: LEDP41.10, RN90.3 (R3.1)
unnamed: LEDP41.11, RN90.2 (R2.1)
unnamed: LEDP41.12, RN90.1 (R1.1)
unnamed: LEDP41.13, RN86.4 (R4.1)
unnamed: LEDP41.14, RN86.3 (R3.1)
unnamed: LEDP41.15, RN86.2 (R2.1)
unnamed: LEDP41.16, RN86.1 (R1.1)
unnamed: LEDP42.9, RN91.4 (R4.1)
unnamed: LEDP42.10, RN91.3 (R3.1)
unnamed: LEDP42.11, RN91.2 (R2.1)
unnamed: LEDP42.12, RN91.1 (R1.1)
unnamed: LEDP42.13, RN87.4 (R4.1)
unnamed: LEDP42.14, RN87.3 (R3.1)
unnamed: LEDP42.15, RN87.2 (R2.1)
unnamed: LEDP42.16, RN87.1 (R1.1)
unnamed: LEDP43.9, RN92.4 (R4.1)
unnamed: LEDP43.10, RN92.3 (R3.1)
unnamed: LEDP43.11, RN92.2 (R2.1)
unnamed: LEDP43.12, RN92.1 (R1.1)
unnamed: LEDP43.13, RN88.4 (R4.1)
unnamed: LEDP43.14, RN88.3 (R3.1)
unnamed: LEDP43.15, RN88.2 (R2.1)
unnamed: LEDP43.16, RN88.1 (R1.1)
unnamed: LEDP44.9, RN93.4 (R4.1)
unnamed: LEDP44.10, RN93.3 (R3.1)
unnamed: LEDP44.11, RN93.2 (R2.1)
unnamed: LEDP44.12, RN93.1 (R1.1)
unnamed: LEDP44.13, RN89.4 (R4.1)
unnamed: LEDP44.14, RN89.3 (R3.1)
unnamed: LEDP44.15, RN89.2 (R2.1)
unnamed: LEDP44.16, RN89.1 (R1.1)
unnamed: LEDP45.9, RN98.4 (R4.1)
unnamed: LEDP45.10, RN98.3 (R3.1)
unnamed: LEDP45.11, RN98.2 (R2.1)
unnamed: LEDP45.12, RN98.1 (R1.1)
unnamed: LEDP45.13, RN94.4 (R4.1)
unnamed: LEDP45.14, RN94.3 (R3.1)
unnamed: LEDP45.15, RN94.2 (R2.1)
unnamed: LEDP45.16, RN94.1 (R1.1)
unnamed: LEDP46.9, RN99.4 (R4.1)
unnamed: LEDP46.10, RN99.3 (R3.1)
unnamed: LEDP46.11, RN99.2 (R2.1)
unnamed: LEDP46.12, RN99.1 (R1.1)
unnamed: LEDP46.13, RN95.4 (R4.1)
unnamed: LEDP46.14, RN95.3 (R3.1)
unnamed: LEDP46.15, RN95.2 (R2.1)
unnamed: LEDP46.16, RN95.1 (R1.1)
unnamed: LEDP47.9, RN100.4 (R4.1)
unnamed: LEDP47.10, RN100.3 (R3.1)
unnamed: LEDP47.11, RN100.2 (R2.1)
unnamed: LEDP47.12, RN100.1 (R1.1)
unnamed: LEDP47.13, RN96.4 (R4.1)
unnamed: LEDP47.14, RN96.3 (R3.1)
unnamed: LEDP47.15, RN96.2 (R2.1)
unnamed: LEDP47.16, RN96.1 (R1.1)
unnamed: LEDP48.9, RN101.4 (R4.1)
unnamed: LEDP48.10, RN101.3 (R3.1)
unnamed: LEDP48.11, RN101.2 (R2.1)
unnamed: LEDP48.12, RN101.1 (R1.1)
unnamed: LEDP48.13, RN97.4 (R4.1)
unnamed: LEDP48.14, RN97.3 (R3.1)
unnamed: LEDP48.15, RN97.2 (R2.1)
unnamed: LEDP48.16, RN97.1 (R1.1)
unnamed: LEDP49.9, RN106.4 (R4.1)
unnamed: LEDP49.10, RN106.3 (R3.1)
unnamed: LEDP49.11, RN106.2 (R2.1)
unnamed: LEDP49.12, RN106.1 (R1.1)
unnamed: LEDP49.13, RN102.4 (R4.1)
unnamed: LEDP49.14, RN102.3 (R3.1)
unnamed: LEDP49.15, RN102.2 (R2.1)
unnamed: LEDP49.16, RN102.1 (R1.1)
unnamed: LEDP50.9, RN107.4 (R4.1)
unnamed: LEDP50.10, RN107.3 (R3.1)
unnamed: LEDP50.11, RN107.2 (R2.1)
unnamed: LEDP50.12, RN107.1 (R1.1)
unnamed: LEDP50.13, RN103.4 (R4.1)
unnamed: LEDP50.14, RN103.3 (R3.1)
unnamed: LEDP50.15, RN103.2 (R2.1)
unnamed: LEDP50.16, RN103.1 (R1.1)
unnamed: LEDP51.9, RN108.4 (R4.1)
unnamed: LEDP51.10, RN108.3 (R3.1)
unnamed: LEDP51.11, RN108.2 (R2.1)
unnamed: LEDP51.12, RN108.1 (R1.1)
unnamed: LEDP51.13, RN104.4 (R4.1)
unnamed: LEDP51.14, RN104.3 (R3.1)
unnamed: LEDP51.15, RN104.2 (R2.1)
unnamed: LEDP51.16, RN104.1 (R1.1)
unnamed: LEDP52.9, RN109.4 (R4.1)
unnamed: LEDP52.10, RN109.3 (R3.1)
unnamed: LEDP52.11, RN109.2 (R2.1)
unnamed: LEDP52.12, RN109.1 (R1.1)
unnamed: LEDP52.13, RN105.4 (R4.1)
unnamed: LEDP52.14, RN105.3 (R3.1)
unnamed: LEDP52.15, RN105.2 (R2.1)
unnamed: LEDP52.16, RN105.1 (R1.1)
unnamed: LEDP53.9, RN114.4 (R4.1)
unnamed: LEDP53.10, RN114.3 (R3.1)
unnamed: LEDP53.11, RN114.2 (R2.1)
unnamed: LEDP53.12, RN114.1 (R1.1)
unnamed: LEDP53.13, RN110.4 (R4.1)
unnamed: LEDP53.14, RN110.3 (R3.1)
unnamed: LEDP53.15, RN110.2 (R2.1)
unnamed: LEDP53.16, RN110.1 (R1.1)
unnamed: LEDP54.9, RN115.4 (R4.1)
unnamed: LEDP54.10, RN115.3 (R3.1)
unnamed: LEDP54.11, RN115.2 (R2.1)
unnamed: LEDP54.12, RN115.1 (R1.1)
unnamed: LEDP54.13, RN111.4 (R4.1)
unnamed: LEDP54.14, RN111.3 (R3.1)
unnamed: LEDP54.15, RN111.2 (R2.1)
unnamed: LEDP54.16, RN111.1 (R1.1)
unnamed: LEDP55.9, RN116.4 (R4.1)
unnamed: LEDP55.10, RN116.3 (R3.1)
unnamed: LEDP55.11, RN116.2 (R2.1)
unnamed: LEDP55.12, RN116.1 (R1.1)
unnamed: LEDP55.13, RN112.4 (R4.1)
unnamed: LEDP55.14, RN112.3 (R3.1)
unnamed: LEDP55.15, RN112.2 (R2.1)
unnamed: LEDP55.16, RN112.1 (R1.1)
unnamed: LEDP56.9, RN117.4 (R4.1)
unnamed: LEDP56.10, RN117.3 (R3.1)
unnamed: LEDP56.11, RN117.2 (R2.1)
unnamed: LEDP56.12, RN117.1 (R1.1)
unnamed: LEDP56.13, RN113.4 (R4.1)
unnamed: LEDP56.14, RN113.3 (R3.1)
unnamed: LEDP56.15, RN113.2 (R2.1)
unnamed: LEDP56.16, RN113.1 (R1.1)
unnamed: LEDP57.9, RN122.4 (R4.1)
unnamed: LEDP57.10, RN122.3 (R3.1)
unnamed: LEDP57.11, RN122.2 (R2.1)
unnamed: LEDP57.12, RN122.1 (R1.1)
unnamed: LEDP57.13, RN118.4 (R4.1)
unnamed: LEDP57.14, RN118.3 (R3.1)
unnamed: LEDP57.15, RN118.2 (R2.1)
unnamed: LEDP57.16, RN118.1 (R1.1)
unnamed: LEDP58.9, RN123.4 (R4.1)
unnamed: LEDP58.10, RN123.3 (R3.1)
unnamed: LEDP58.11, RN123.2 (R2.1)
unnamed: LEDP58.12, RN123.1 (R1.1)
unnamed: LEDP58.13, RN119.4 (R4.1)
unnamed: LEDP58.14, RN119.3 (R3.1)
unnamed: LEDP58.15, RN119.2 (R2.1)
unnamed: LEDP58.16, RN119.1 (R1.1)
unnamed: LEDP59.9, RN124.4 (R4.1)
unnamed: LEDP59.10, RN124.3 (R3.1)
unnamed: LEDP59.11, RN124.2 (R2.1)
unnamed: LEDP59.12, RN124.1 (R1.1)
unnamed: LEDP59.13, RN120.4 (R4.1)
unnamed: LEDP59.14, RN120.3 (R3.1)
unnamed: LEDP59.15, RN120.2 (R2.1)
unnamed: LEDP59.16, RN120.1 (R1.1)
unnamed: LEDP60.9, RN125.4 (R4.1)
unnamed: LEDP60.10, RN125.3 (R3.1)
unnamed: LEDP60.11, RN125.2 (R2.1)
unnamed: LEDP60.12, RN125.1 (R1.1)
unnamed: LEDP60.13, RN121.4 (R4.1)
unnamed: LEDP60.14, RN121.3 (R3.1)
unnamed: LEDP60.15, RN121.2 (R2.1)
unnamed: LEDP60.16, RN121.1 (R1.1)
unnamed: LEDP61.9, RN130.4 (R4.1)
unnamed: LEDP61.10, RN130.3 (R3.1)
unnamed: LEDP61.11, RN130.2 (R2.1)
unnamed: LEDP61.12, RN130.1 (R1.1)
unnamed: LEDP61.13, RN126.4 (R4.1)
unnamed: LEDP61.14, RN126.3 (R3.1)
unnamed: LEDP61.15, RN126.2 (R2.1)
unnamed: LEDP61.16, RN126.1 (R1.1)
unnamed: LEDP62.9, RN131.4 (R4.1)
unnamed: LEDP62.10, RN131.3 (R3.1)
unnamed: LEDP62.11, RN131.2 (R2.1)
unnamed: LEDP62.12, RN131.1 (R1.1)
unnamed: LEDP62.13, RN127.4 (R4.1)
unnamed: LEDP62.14, RN127.3 (R3.1)
unnamed: LEDP62.15, RN127.2 (R2.1)
unnamed: LEDP62.16, RN127.1 (R1.1)
unnamed: LEDP63.9, RN132.4 (R4.1)
unnamed: LEDP63.10, RN132.3 (R3.1)
unnamed: LEDP63.11, RN132.2 (R2.1)
unnamed: LEDP63.12, RN132.1 (R1.1)
unnamed: LEDP63.13, RN128.4 (R4.1)
unnamed: LEDP63.14, RN128.3 (R3.1)
unnamed: LEDP63.15, RN128.2 (R2.1)
unnamed: LEDP63.16, RN128.1 (R1.1)
unnamed: LEDP64.9, RN133.4 (R4.1)
unnamed: LEDP64.10, RN133.3 (R3.1)
unnamed: LEDP64.11, RN133.2 (R2.1)
unnamed: LEDP64.12, RN133.1 (R1.1)
unnamed: LEDP64.13, RN129.4 (R4.1)
unnamed: LEDP64.14, RN129.3 (R3.1)
unnamed: LEDP64.15, RN129.2 (R2.1)
unnamed: LEDP64.16, RN129.1 (R1.1)
~RST: U17.23 (RSTN), U18.23 (RSTN), U19.23 (RSTN), U20.23 (RSTN), U21.23 (RSTN), U22.23 (RSTN), U23.23 (RSTN), U24.23 (RSTN), U25.23 (RSTN), U26.23 (RSTN), U27.23 (RSTN), U28.23 (RSTN), U29.23 (RSTN), U30.23 (RSTN), U31.23 (RSTN), U32.23 (RSTN); also elsewhere on the board

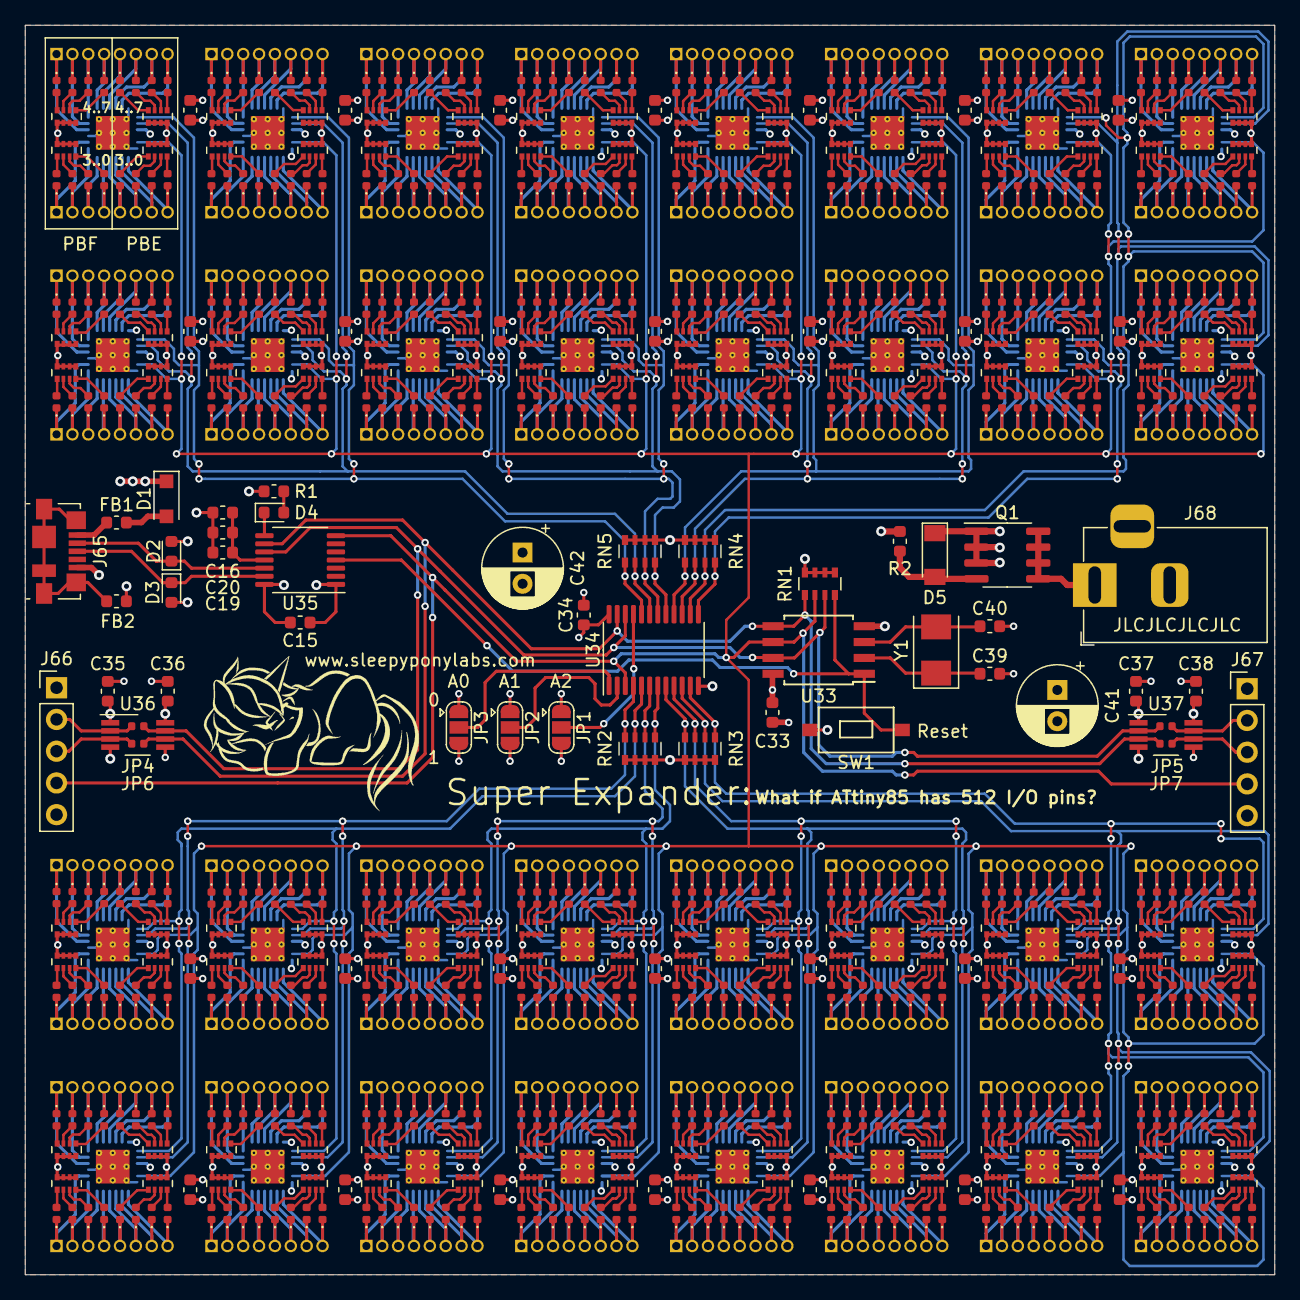
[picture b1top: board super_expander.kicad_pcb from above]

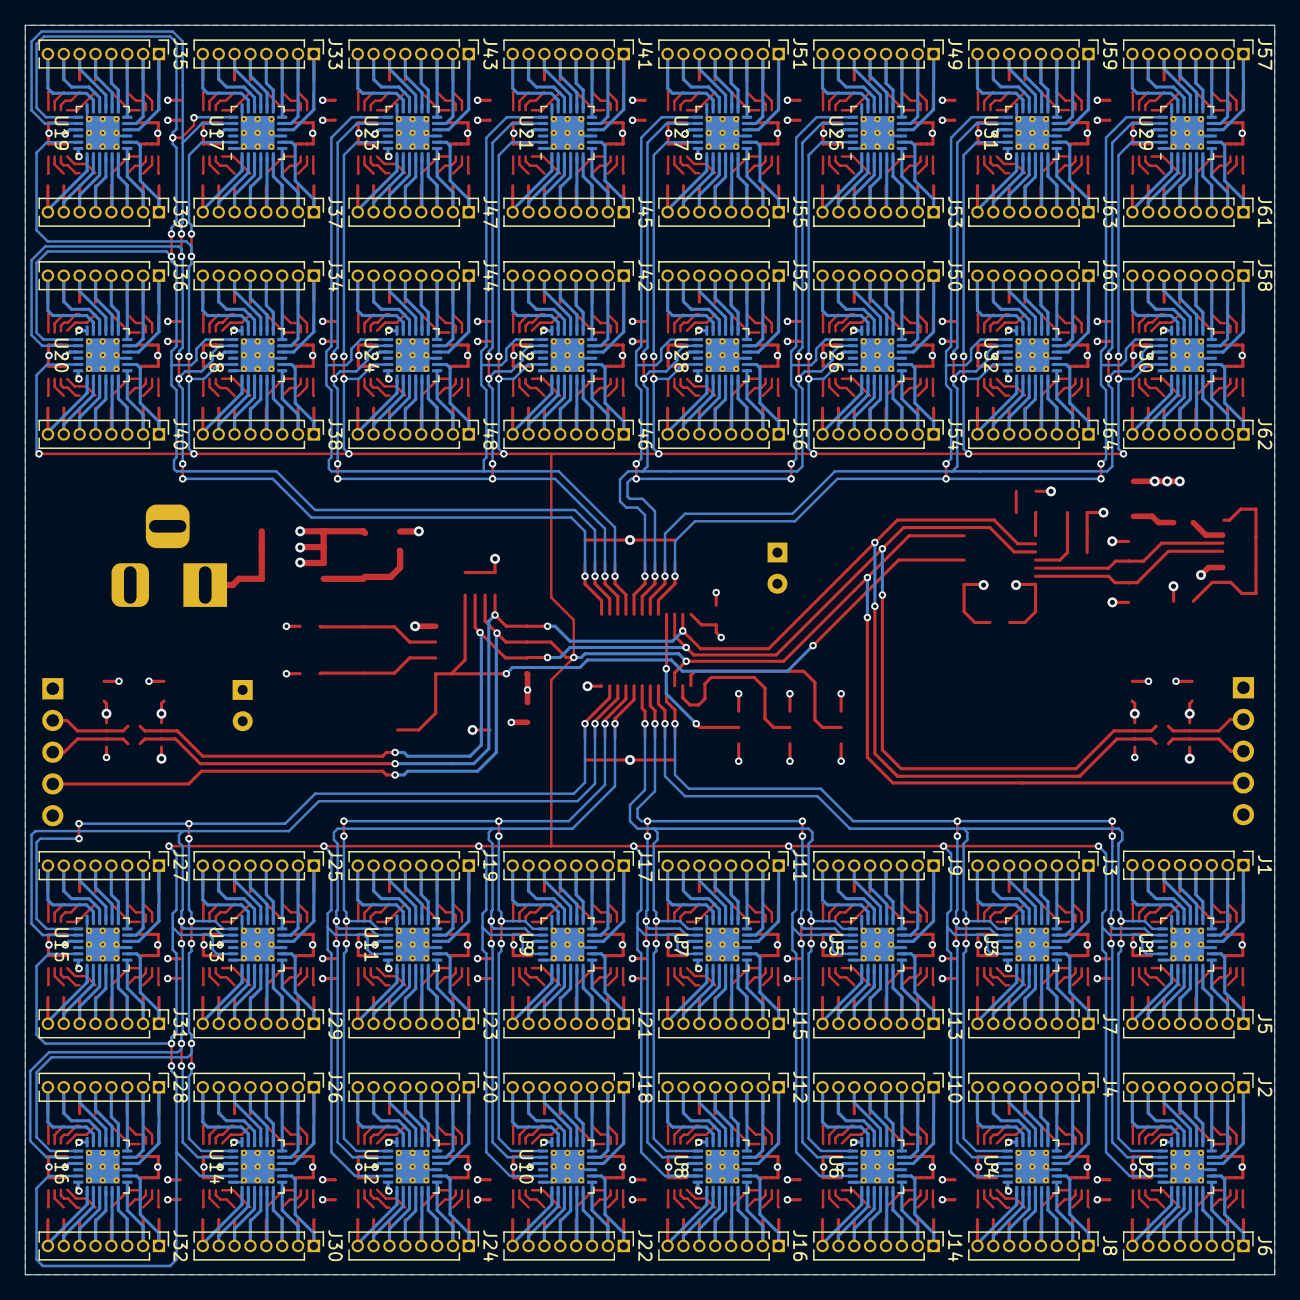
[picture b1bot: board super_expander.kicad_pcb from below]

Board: 4 copper layers, 100.0 x 100.0 mm, 363 parts (96 on the bottom side), 1065 nets.

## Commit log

2021-03-12 PCB routing progress
2021-03-13 Continue Routing
2021-03-14 version 1
2021-03-14 Add programming header
2021-03-14 Change some C and R values
